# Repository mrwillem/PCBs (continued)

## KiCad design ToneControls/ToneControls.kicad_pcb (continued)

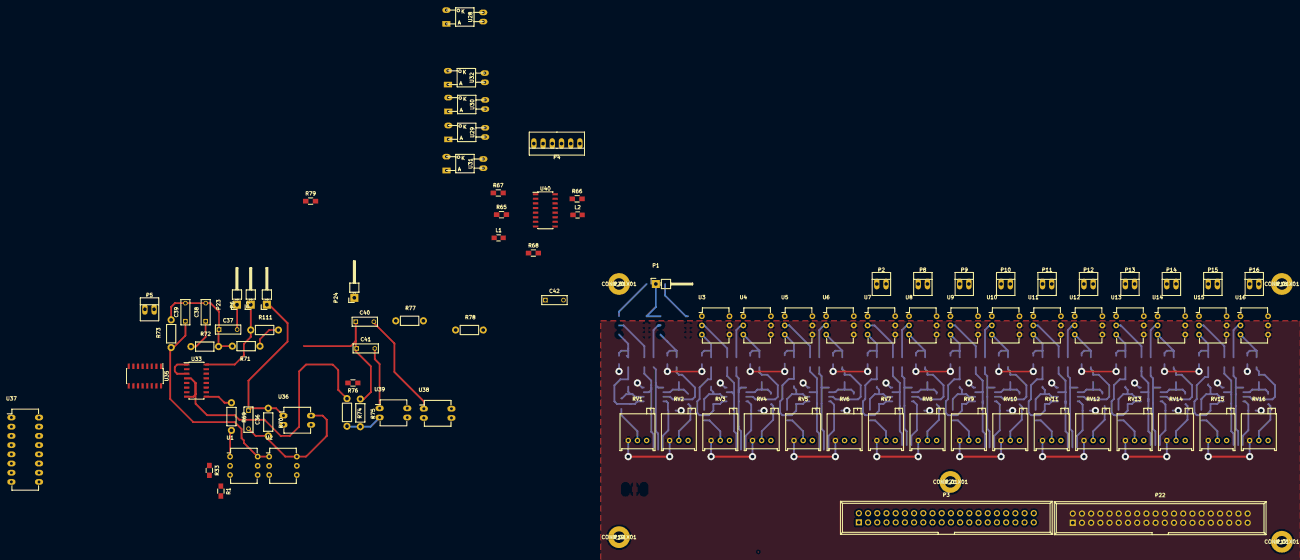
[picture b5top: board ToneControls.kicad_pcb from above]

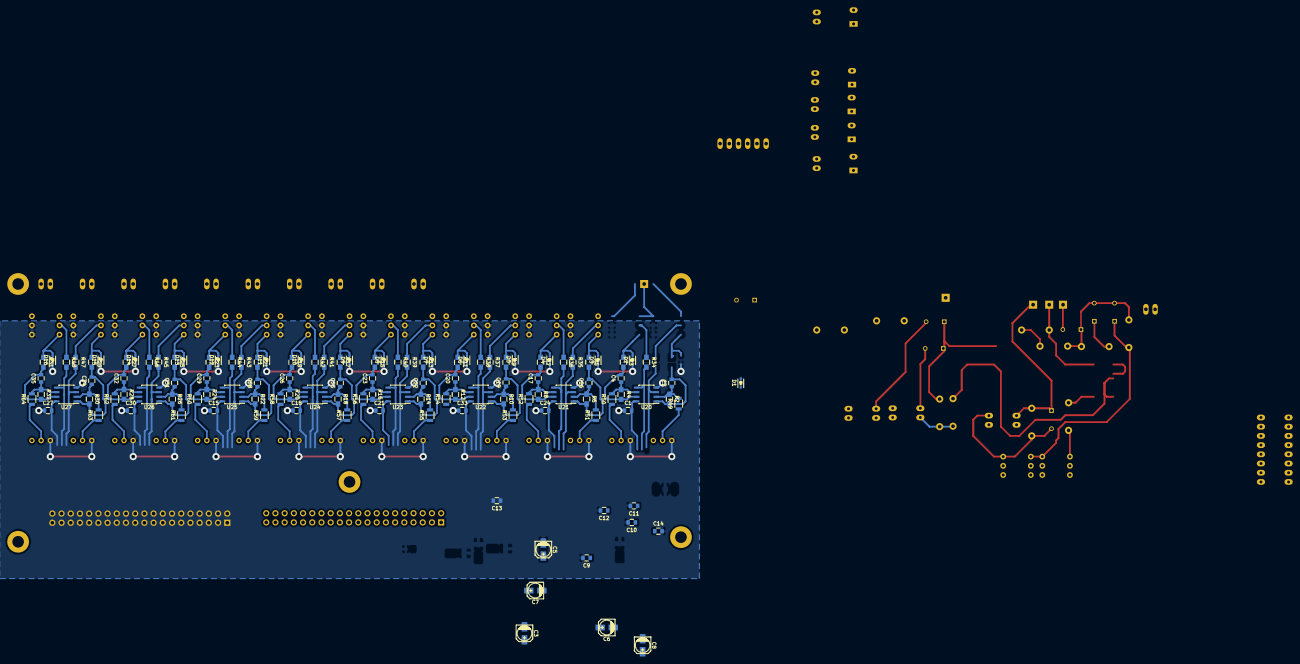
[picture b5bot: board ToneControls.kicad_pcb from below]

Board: 2 copper layers, 216 parts (121 on the bottom side), 160 nets.

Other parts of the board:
P9, P10: CONN_01X02; PINHEAD1-2

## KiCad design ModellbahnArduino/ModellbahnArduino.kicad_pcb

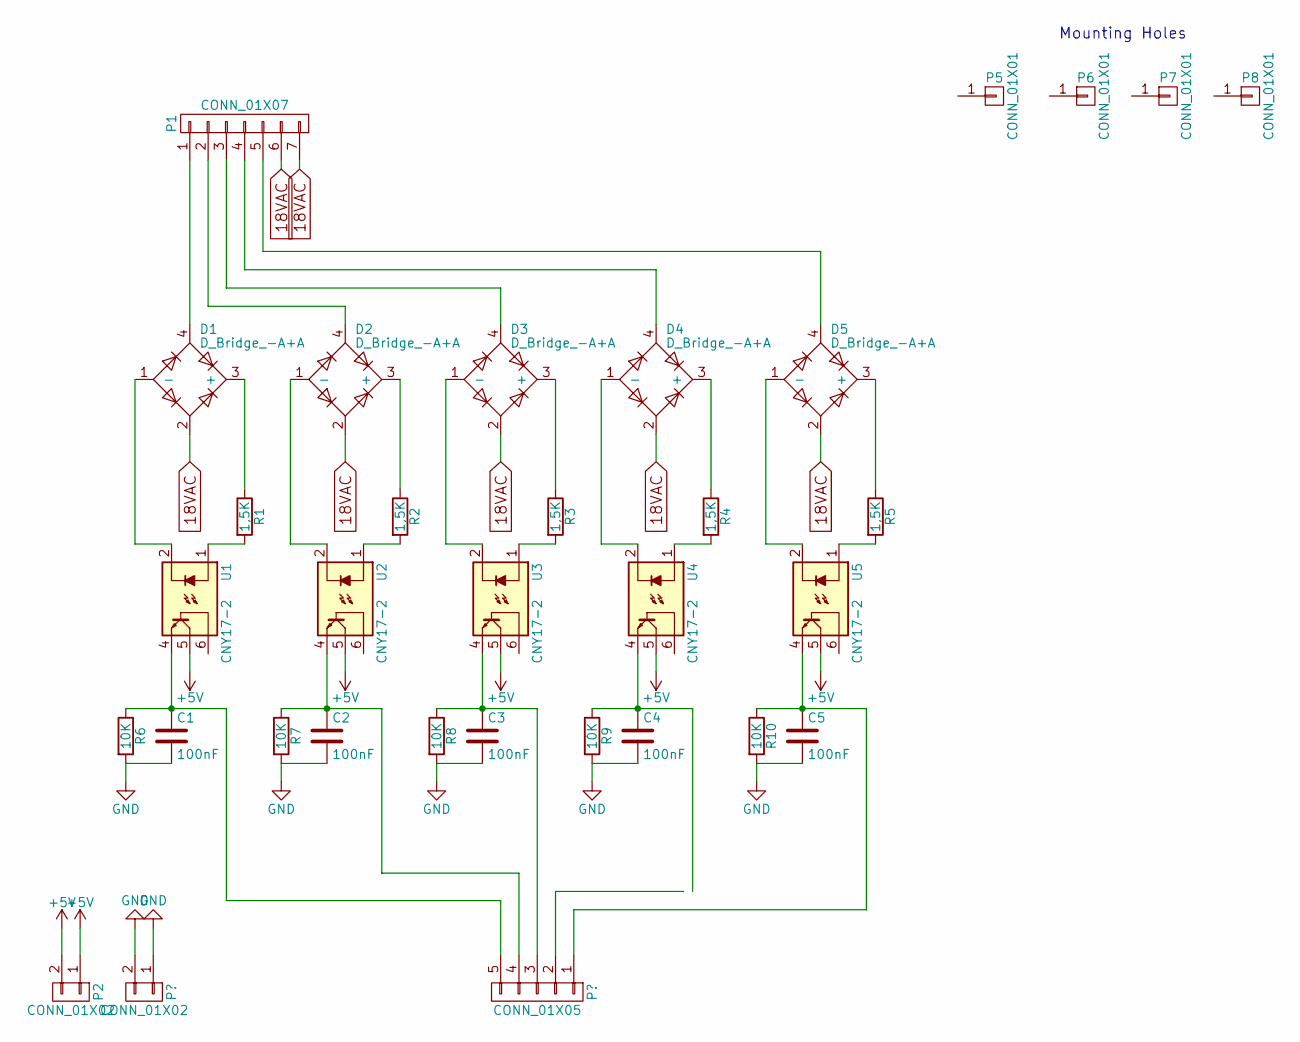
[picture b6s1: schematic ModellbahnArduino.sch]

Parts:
C1, C2, C3, C4, C5: 100nF; C_Disc_D5.0mm_W2.5mm_P2.50mm
D1, D2, D3, D4, D5: D_Bridge_-A+A; Diode_Bridge_9mm
P1: CONN_01X07; Pin_Header_Straight_1x07_Pitch2.54mm
P2: CONN_01X02; Pin_Header_Straight_1x02_Pitch2.54mm
P5, P6, P7, P8: CONN_01X01; MountingHole_3.2mm_M3_ISO7380
R1, R2, R3, R4, R5: 1,5K; R_Axial_DIN0207_L6.3mm_D2.5mm_P7.62mm_Horizontal
R6, R7, R8, R9, R10: 10K; R_Axial_DIN0207_L6.3mm_D2.5mm_P7.62mm_Horizontal
U1, U2, U3, U4, U5: CNY17-2; DIP-6_W7.62mm_LongPads

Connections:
18VAC: D1.2, D2.2, D3.2, D4.2, D5.2, P1.6, P1.7; also elsewhere on the board
+5V: P2.1, P2.2, U1.5, U2.5, U3.5, U4.5, U5.5
GND: C1.2, C2.2, C3.2, C4.2, C5.2, R6.2, R7.2, R8.2, R9.2, R10.2; also elsewhere on the board
unnamed: D1.1 (-), U1.2
unnamed: D1.3 (+), R1.1
unnamed: D1.4, P1.1
unnamed: D2.1 (-), U2.2
unnamed: D2.3 (+), R2.1
unnamed: D2.4, P1.2
unnamed: D3.1 (-), U3.2
unnamed: D3.3 (+), R3.1
unnamed: D3.4, P1.3
unnamed: D4.1 (-), U4.2
unnamed: D4.3 (+), R4.1
unnamed: D4.4, P1.4
unnamed: D5.1 (-), U5.2
unnamed: D5.3 (+), R5.1
unnamed: D5.4, P1.5
unnamed: R1.2, U1.1
unnamed: R2.2, U2.1
unnamed: R3.2, U3.1
unnamed: R4.2, U4.1
unnamed: R5.2, U5.1
OUT1: C1.1, R6.1, U1.4; also elsewhere on the board
OUT2: C2.1, R7.1, U2.4; also elsewhere on the board
OUT3: C3.1, R8.1, U3.4; also elsewhere on the board
OUT4: C4.1, R9.1, U4.4; also elsewhere on the board
OUT5: C5.1, R10.1, U5.4; also elsewhere on the board

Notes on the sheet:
Mounting Holes

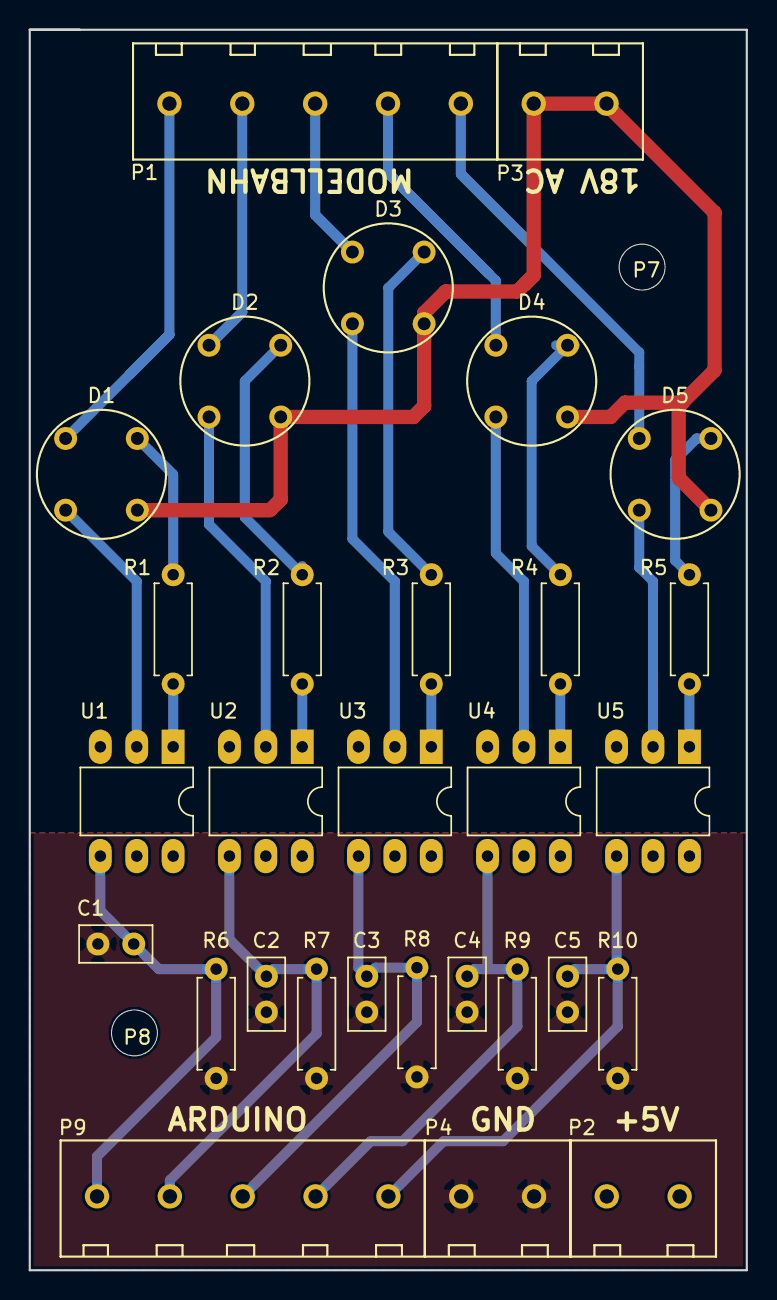
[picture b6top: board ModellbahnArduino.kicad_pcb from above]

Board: 2 copper layers, 50.0 x 86.5 mm, 32 parts (0 on the bottom side), 28 nets.

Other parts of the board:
P3, P4: CONN_01X02; Pin_Header_Straight_1x02_Pitch5.08mmDegson
P9: CONN_01X05; Pin_Header_Straight_1x05_Pitch5.08mmDegson

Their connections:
18VAC: P3.1, P3.2; also elsewhere on the board
GND: P4.1, P4.2; also elsewhere on the board
OUT1: P9.1; also elsewhere on the board
OUT2: P9.2; also elsewhere on the board
OUT3: P9.3; also elsewhere on the board
OUT4: P9.4; also elsewhere on the board
OUT5: P9.5; also elsewhere on the board

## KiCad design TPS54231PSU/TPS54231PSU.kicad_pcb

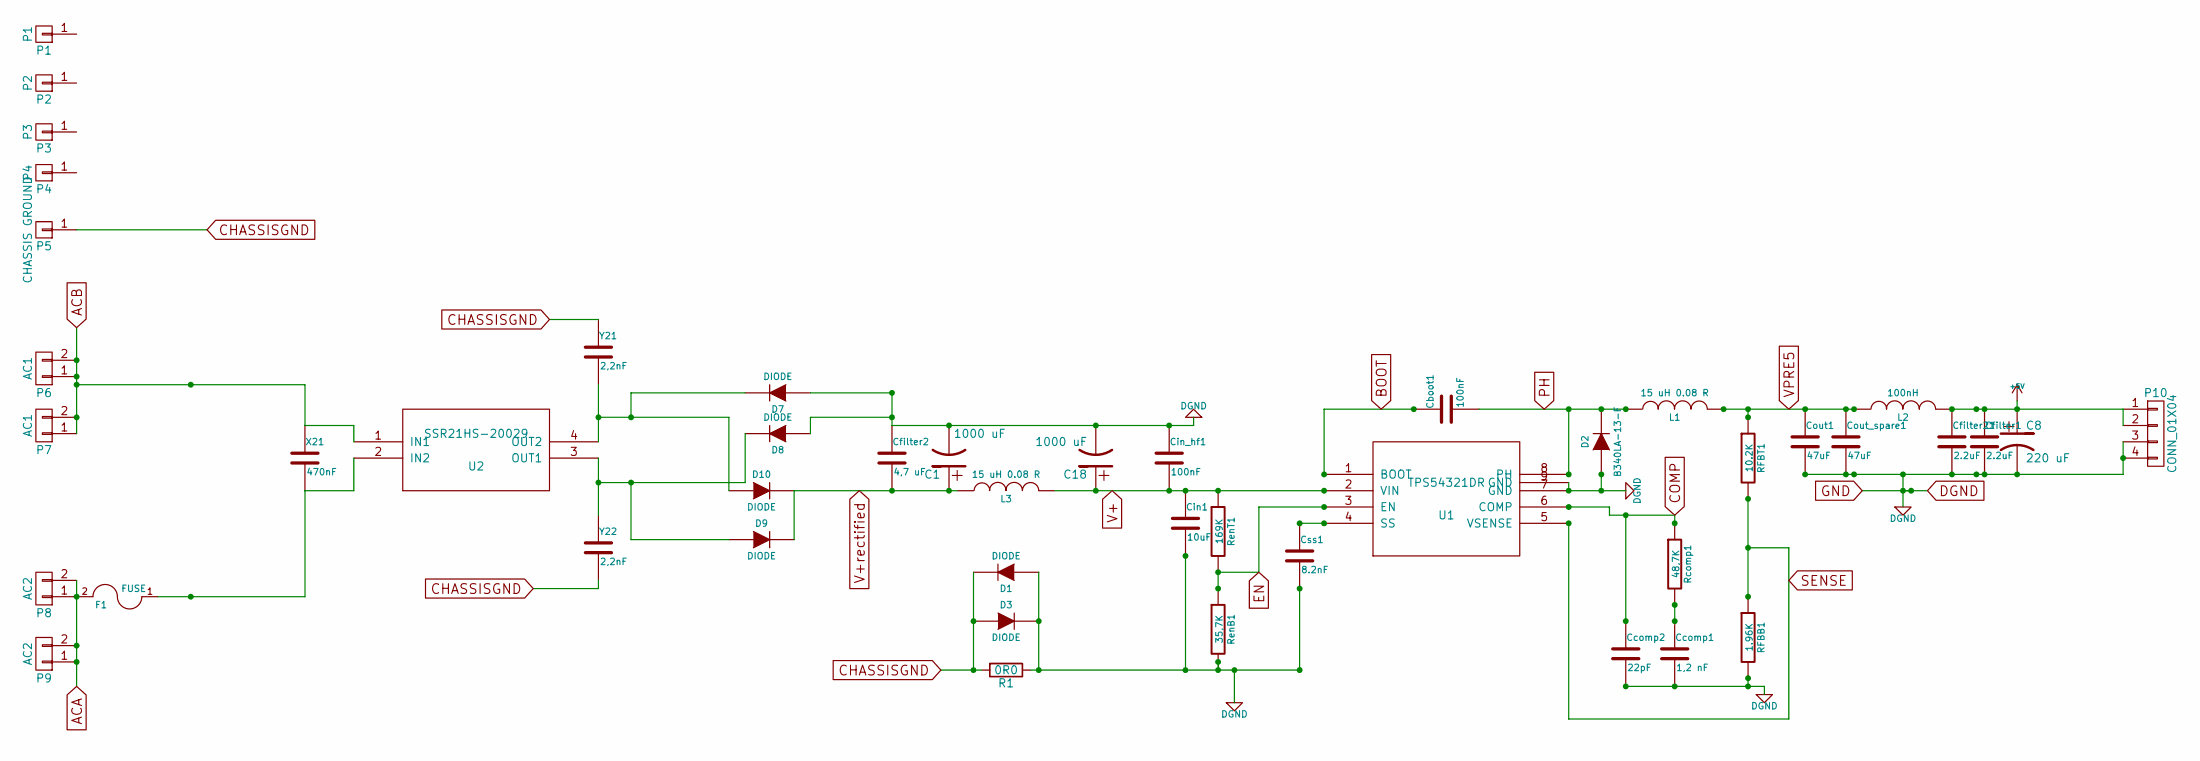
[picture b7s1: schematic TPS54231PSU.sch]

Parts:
C1, C18: 1000 uF; c_elec_12,5x15
C8: 220 uF; c_elec_8x10.5
Cboot1: 100nF; C_0805
Ccomp1: 1,2 nF; C_0805
Ccomp2: 22pF; C_0805
Cfilter1, Cfilter21: 2.2uF; C_0805
Cfilter2: 4,7 uF; C_1206
Cin1: 10uF; C_1206
Cin_hf1: 100nF; C_0805
Cout1: 47uF; C_1206
Cout_spare1: 47uF; C_1206
Css1: 8.2nF; C_0805
D1, D3, D7, D8, D9, D10: DIODE; SMA_Handsoldering
D2: B340LA-13-F; SMA_Handsoldering
F1: FUSE; FSUPCMS
L1, L3: 15 uH 0.08 R; inductor_bourns_16uH
L2: 100nH; Choke_SMD_Wuerth-WE-PD-Typ-M-Typ-S_Handsoldering_RevA_27Jul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
P1: P1; hole
P2: P2; hole
P3: P3; hole
P4: P4; hole
P5: CHASSIS GROUND; M4_Connect_Hole
P6, P7: AC1; Flat_Connector_635mm_
P8, P9: AC2; Flat_Connector_635mm_
P10: CONN_01X04; PINHEAD1-4
R1: 0R0; R_1206
RFBB1: 1.96K; R_0805
RFBT1: 10.2K; R_0805
Rcomp1: 48,7K; R_0805
RenB1: 35,7K; R_0805
RenT1: 169K; R_0805
U1: TPS54321DR; SOIC-8-1EP_3.9x4.9mm_Pitch1.27mm
U2: SSR21HS-20029; CommonModeChoke_KEMET_SSR21HS
X21: 470nF; C_Rect_L27_W9_H17_P23
Y21, Y22: 2,2nF; C_Rect_L18_W5_P15

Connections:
+5V: C8.1, Cfilter1.1, Cfilter21.1, L2.2, P10.1, P10.2
ACA: F1.2, P8.1, P8.2, P9.1, P9.2
ACB: P6.1, P6.2, P7.1, P7.2, U2.1 (IN1), X21.1
BOOT: Cboot1.1, U1.1 (BOOT)
CHASSISGND: D1.2 (K), D3.1 (A), P5.1, R1.2, Y21.1, Y22.2
COMP: Ccomp2.1, Rcomp1.1, U1.6 (COMP)
DGND: C1.2, C8.2, C18.2, Ccomp1.2, Ccomp2.2, Cfilter1.2, Cfilter2.1, Cfilter21.2, Cin1.2, Cin_hf1.1, Cout1.2, Cout_spare1.2, Css1.2, D1.1 (A), D2.1 (A), D3.2 (K), D7.1 (A), D8.1 (A), P10.3, P10.4, R1.1, RFBB1.2, RenB1.2, U1.7 (GND), U1.9 (GND)
EN: RenB1.1, RenT1.2, U1.3 (EN)
unnamed: Ccomp1.1, Rcomp1.2
unnamed: Css1.1, U1.4 (SS)
unnamed: D8.2 (K), D9.1 (A), U2.3 (OUT1), Y22.1
unnamed: D7.2 (K), D10.1 (A), U2.4 (OUT2), Y21.2
unnamed: F1.1, U2.2 (IN2), X21.2
PH: Cboot1.2, D2.2 (K), L1.1, U1.8 (PH)
SENSE: RFBB1.1, RFBT1.2, U1.5 (VSENSE)
V+: C18.1, Cin1.1, Cin_hf1.2, L3.2, RenT1.1, U1.2 (VIN)
V+rectified: C1.1, Cfilter2.2, D9.2 (K), D10.2 (K), L3.1
VPRE5: Cout1.1, Cout_spare1.1, L1.2, L2.1, RFBT1.1

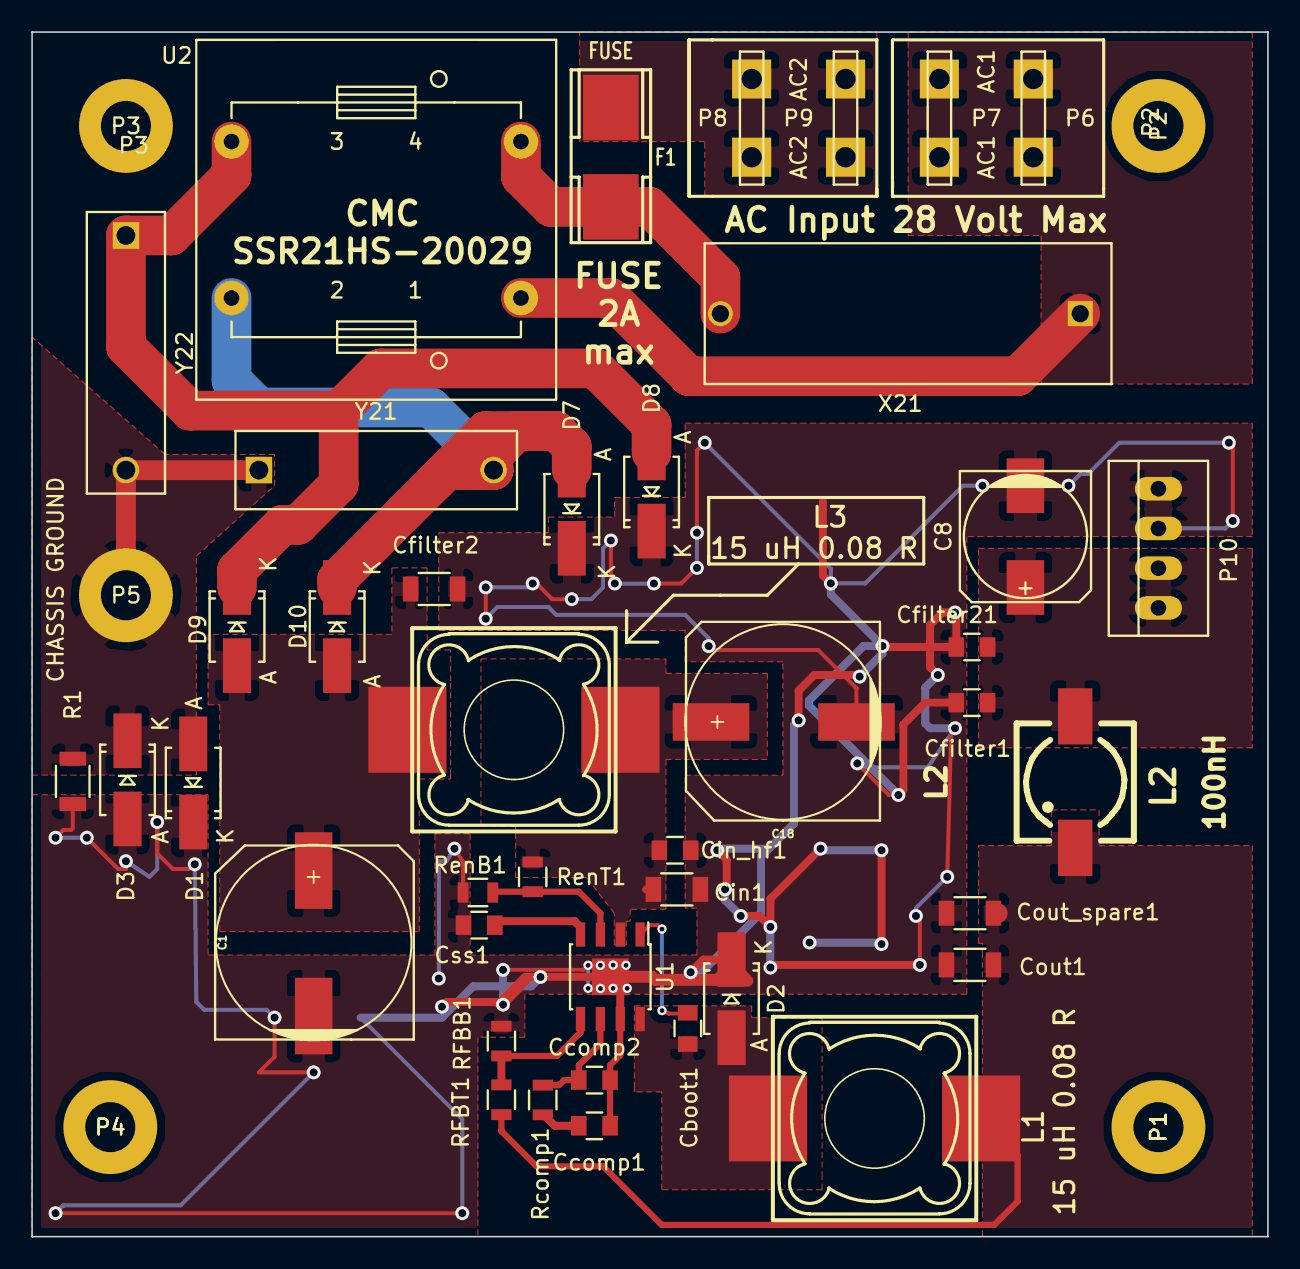
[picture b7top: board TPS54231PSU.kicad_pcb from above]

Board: 4 copper layers, 79.0 x 77.0 mm, 46 parts (0 on the bottom side), 18 nets.

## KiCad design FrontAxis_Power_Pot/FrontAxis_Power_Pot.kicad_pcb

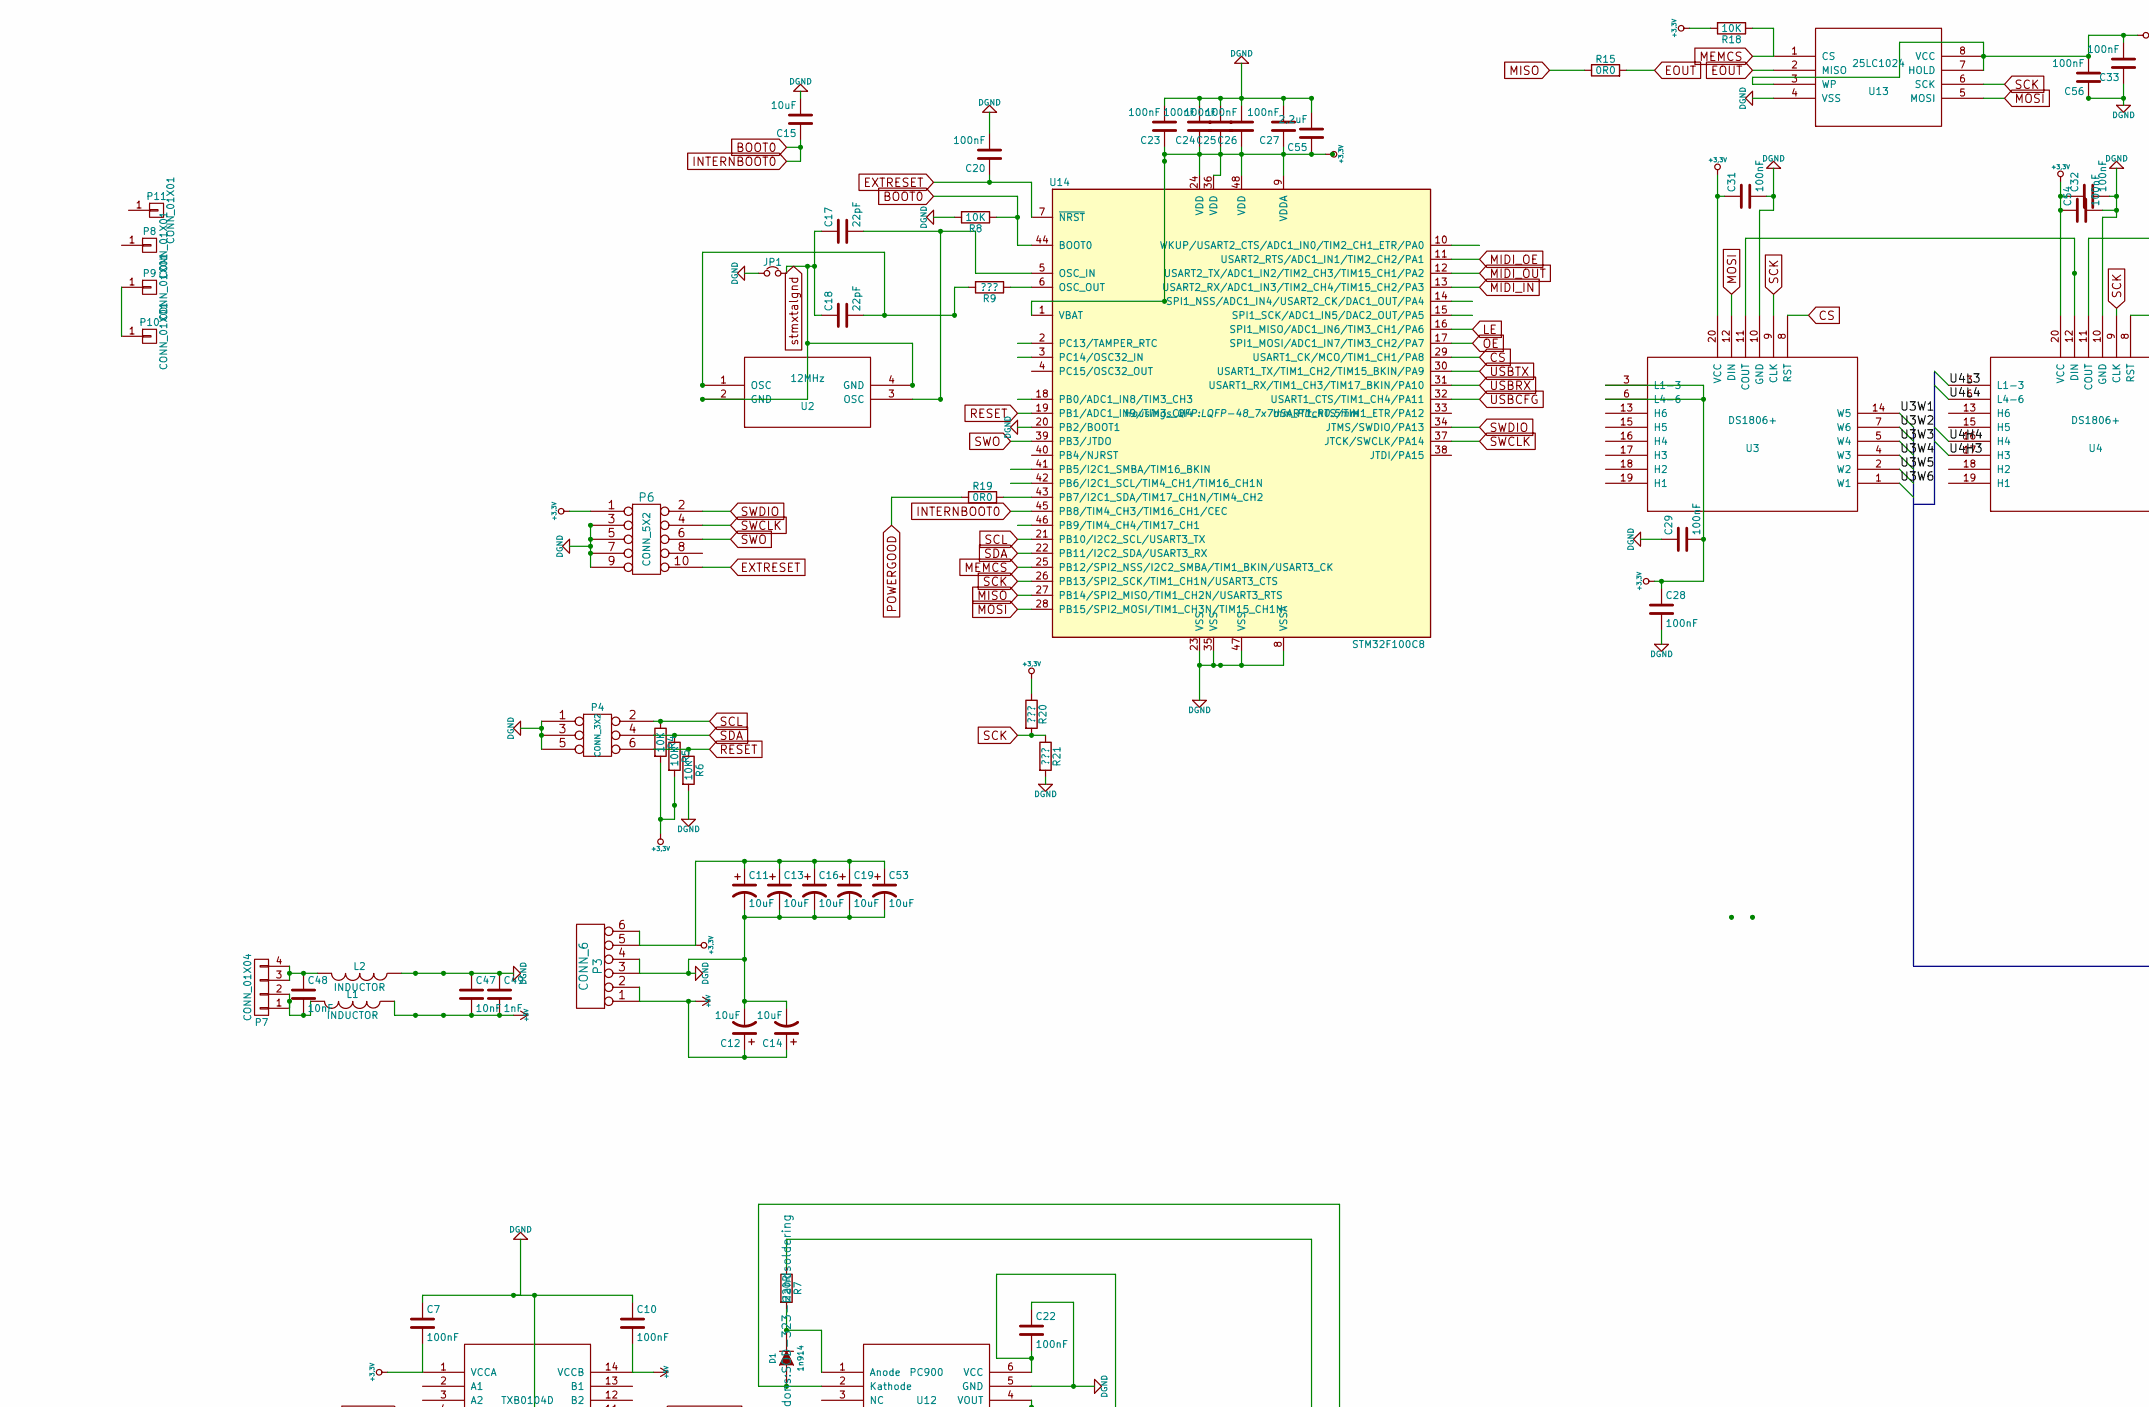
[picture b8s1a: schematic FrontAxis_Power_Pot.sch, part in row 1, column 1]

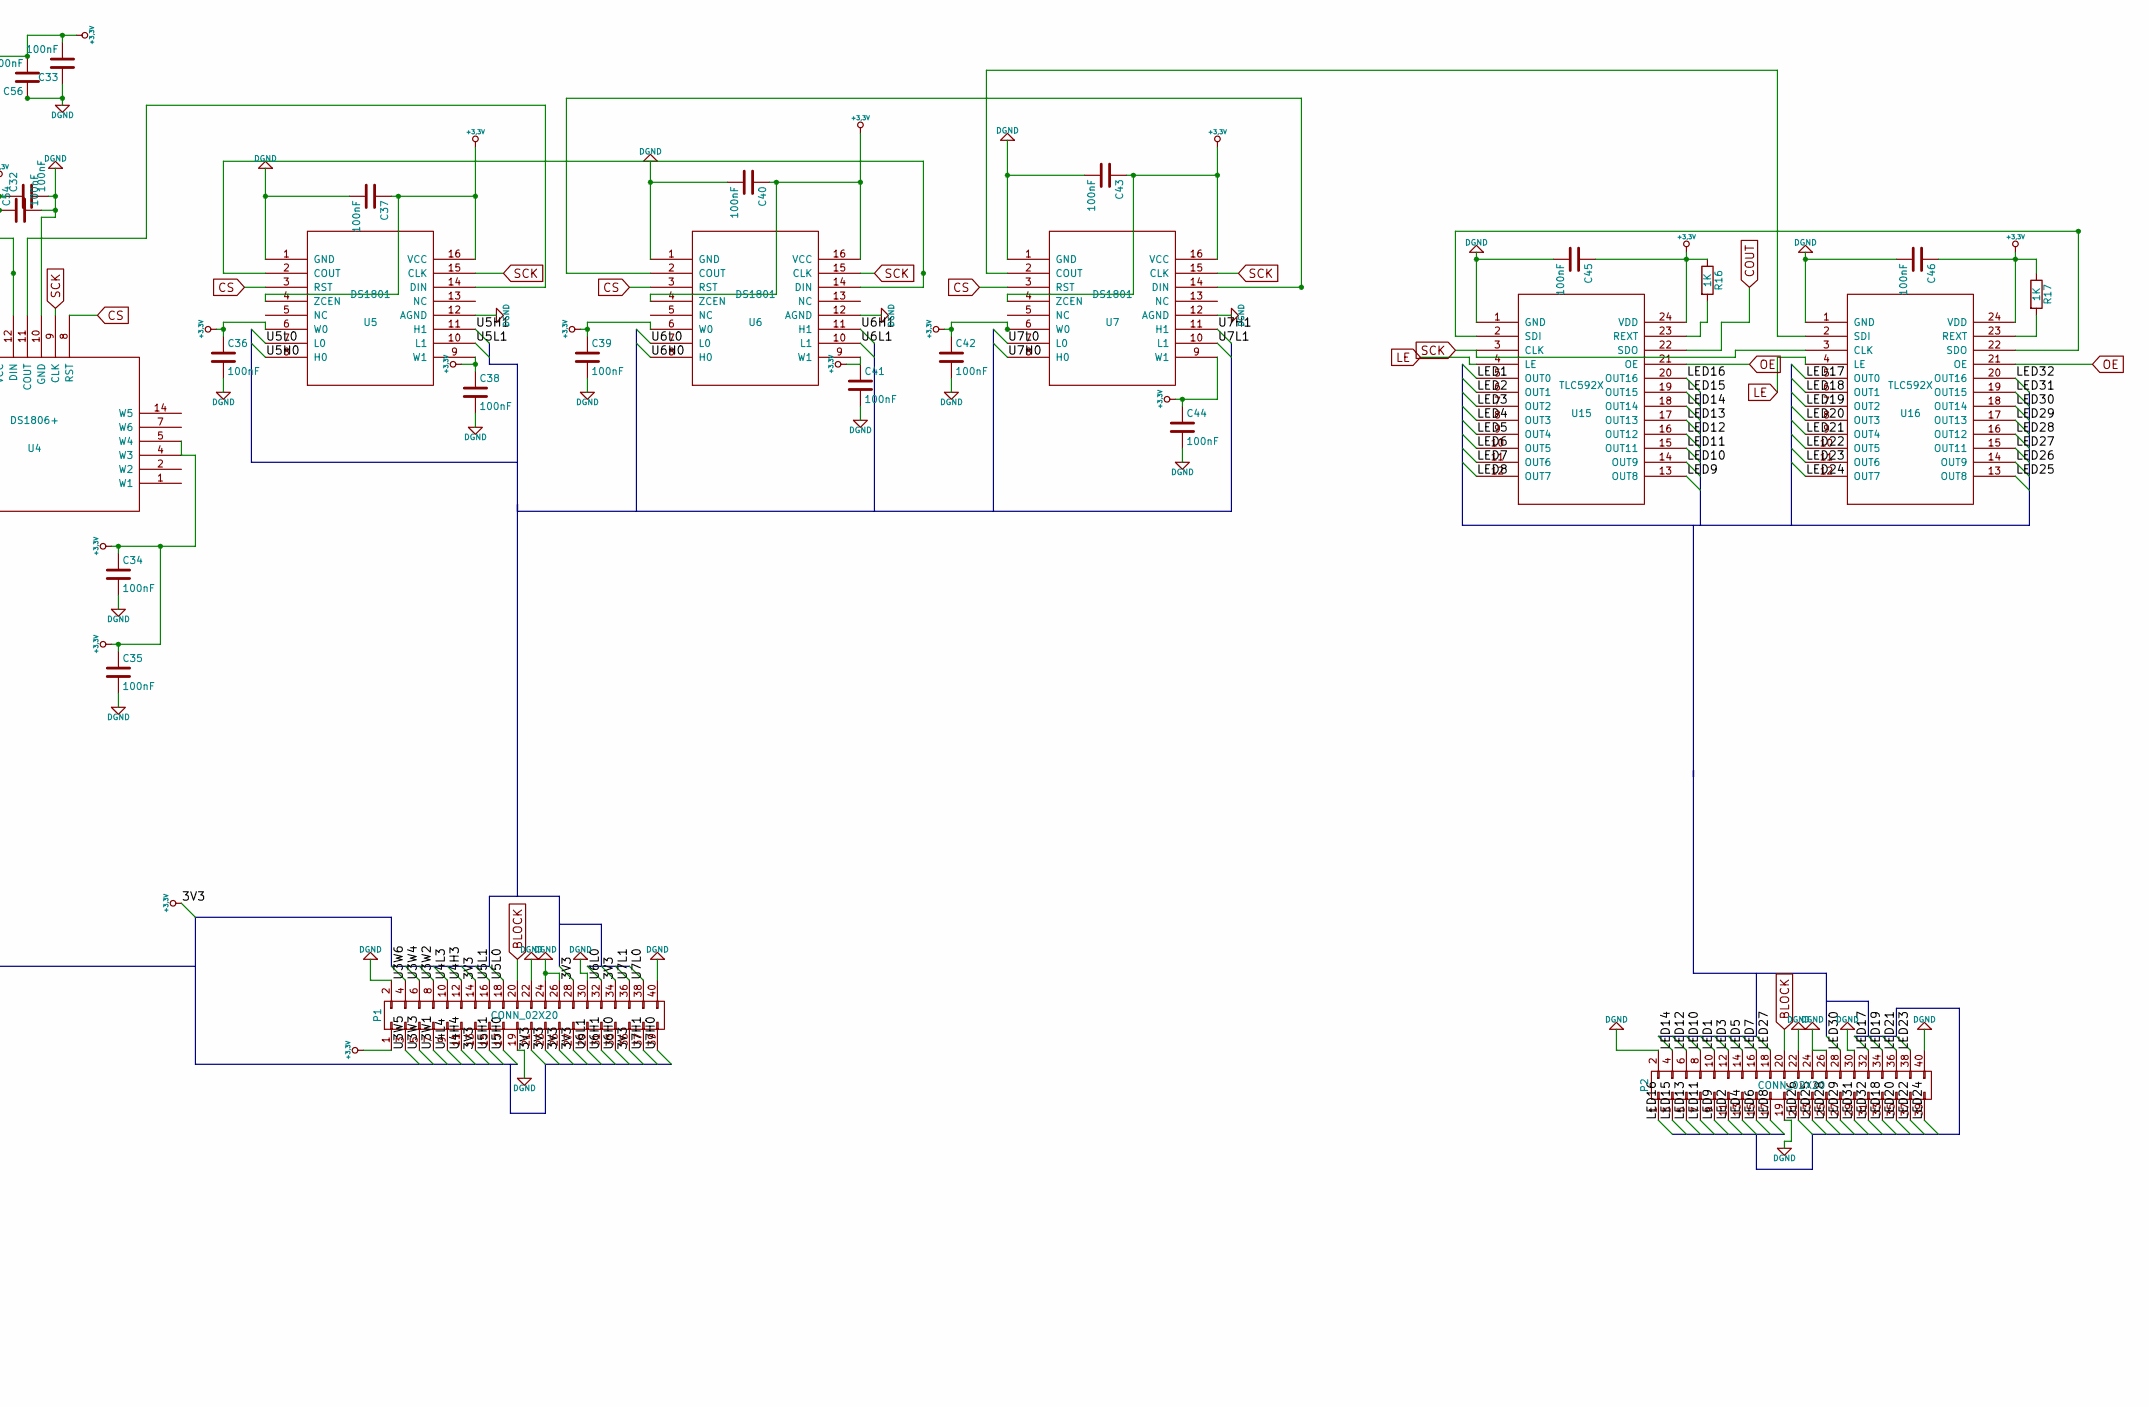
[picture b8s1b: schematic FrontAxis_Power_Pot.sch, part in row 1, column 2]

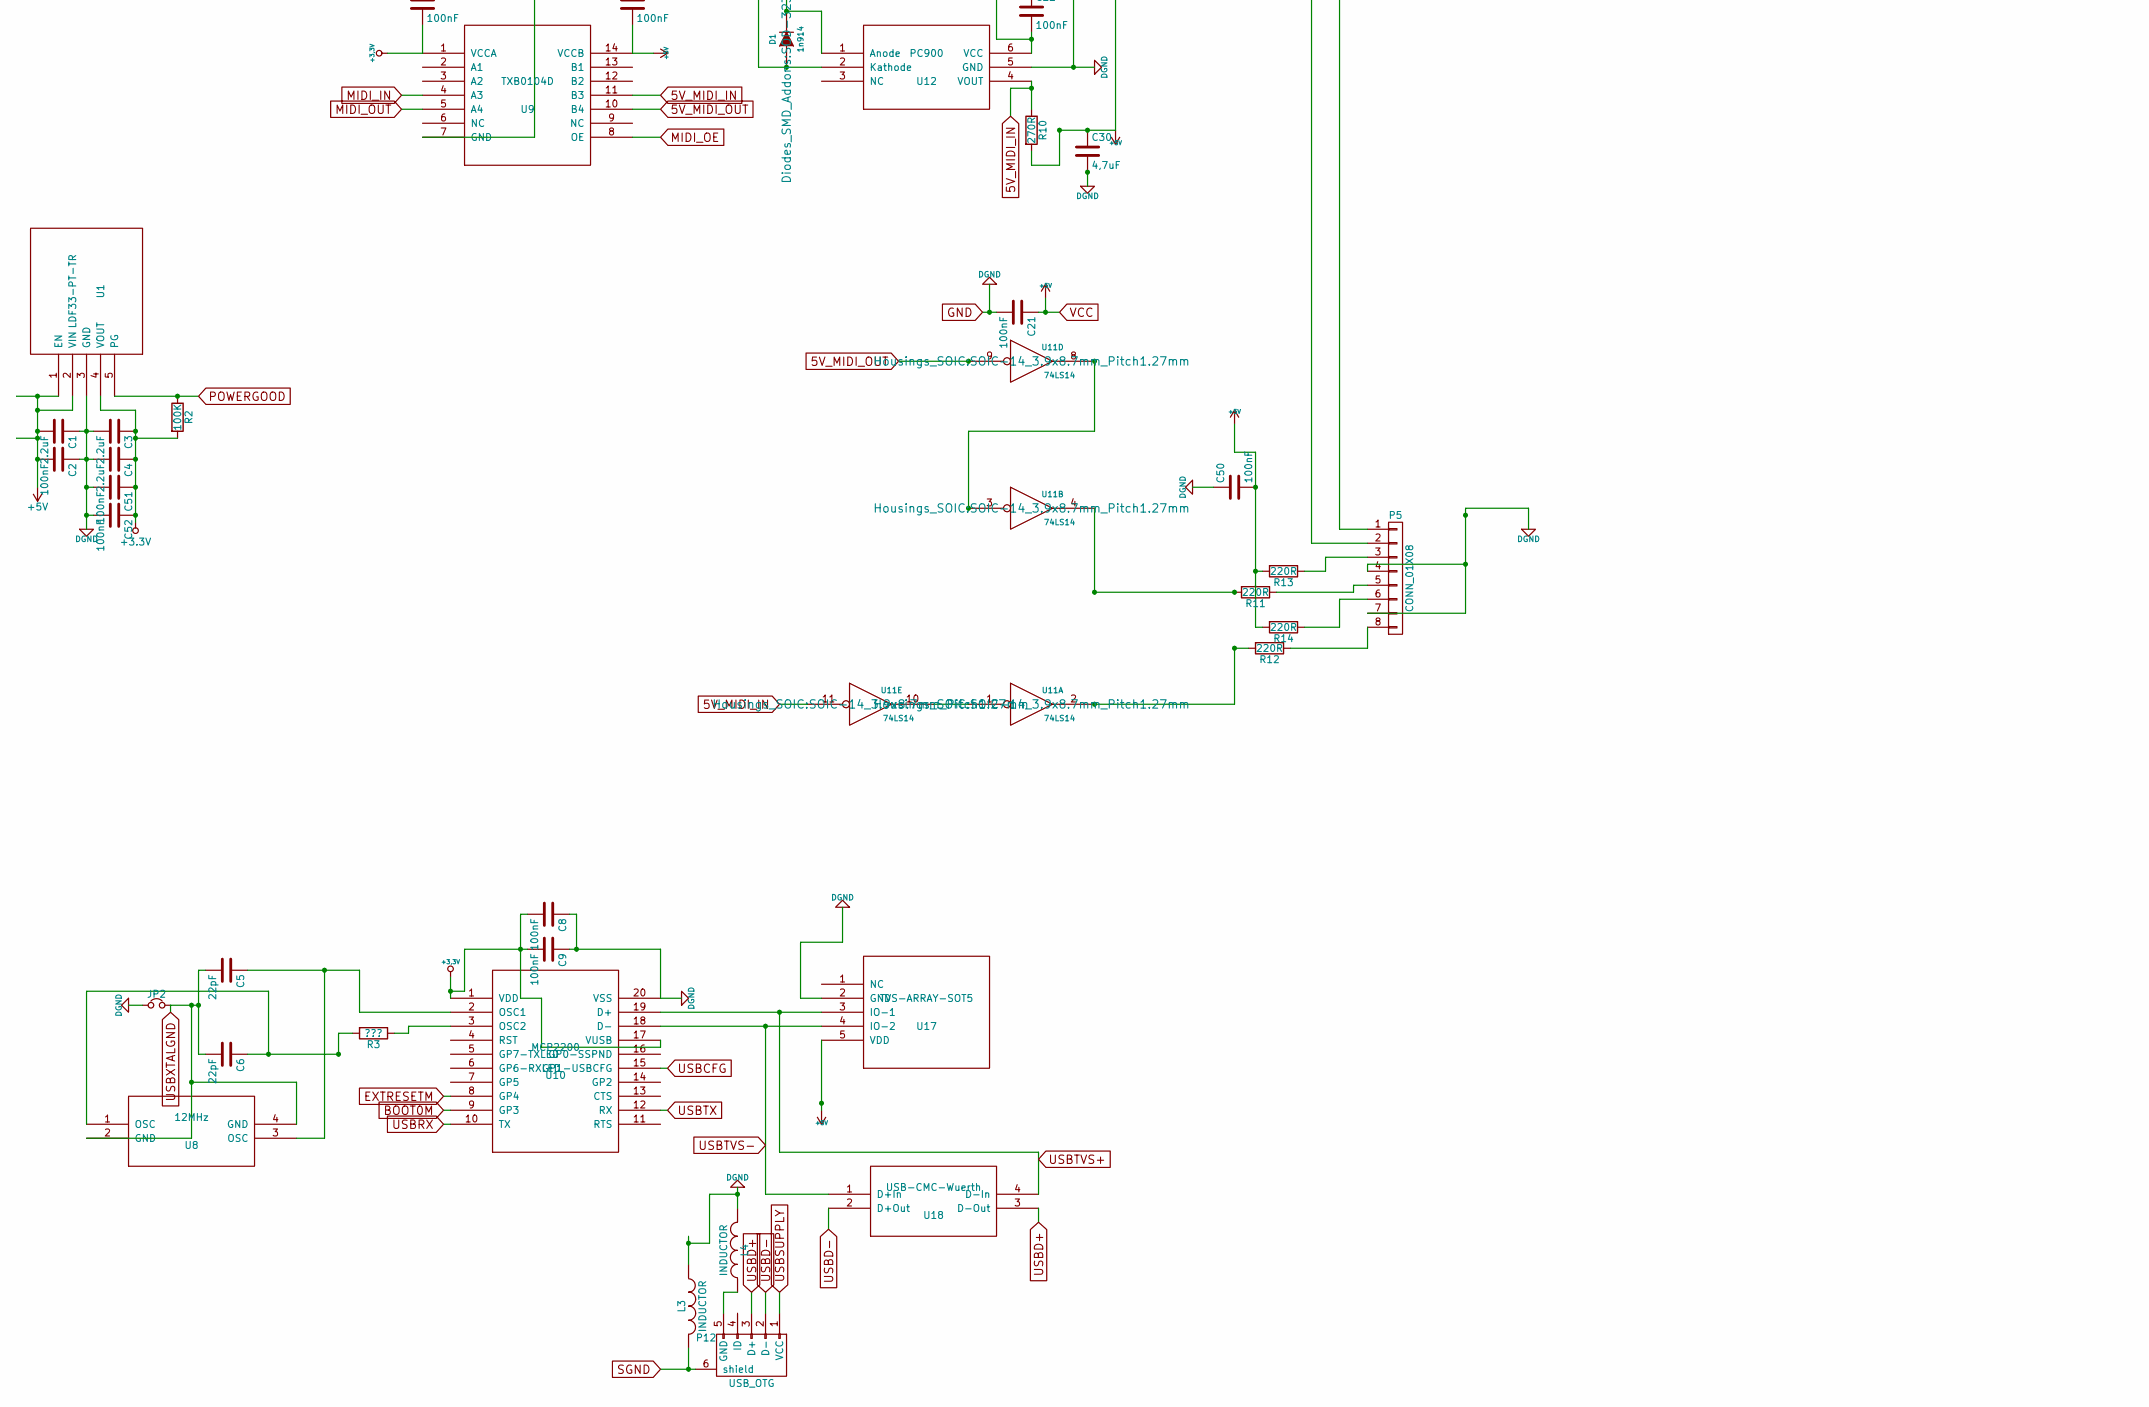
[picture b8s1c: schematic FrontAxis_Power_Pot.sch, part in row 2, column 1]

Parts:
C1, C3, C4: 2.2uF; C_0805
C2, C7, C8, C9, C10, C20, C21, C22, C23, C24, C25, C26, C27, C28, C29, C31, C32, C33, C34, C35, C36, C37, C38, C39, C40, C41, C42, C43, C44, C45, C46, C50, C51, C52, C54, C56: 100nF; C_0805
C5, C6, C17, C18: 22pF; C_0805
C11, C12, C13, C14, C16, C19, C53: 10uF; c_elec_4x5.8
C15: 10uF; C_1210
C30: 4,7uF; C_1210
C47, C48: 10nF; C_0805
C49: 1nF; C_0805
C55: 2,2uF; C_0805
D1: 1n914; SOD-323-Handsoldering
JP1, JP2: Jumper_NC_Small; NetTie-I_Connected_SMD
L1, L2: INDUCTOR; Choke_SMD_1206_Standard
L3, L4: INDUCTOR; C_0805
P1, P2: CONN_02X20; IDC_Header_Straight_40pins
P3: CONN_6; PINHEAD1-6
P4: CONN_3X2; con-amp-micromatch-MICROMATCH-6-correct
P5: CONN_01X08; PINHEAD1-8
P6: CONN_5X2; Pin_Header_Straight_2x05_Pitch1.27mm
P7: CONN_01X04; PINHEAD1-4
P8, P9, P10, P11: CONN_01X01; hole
P12: USB_OTG; USB_Mini-B
R2: 100K; R_0805_HandSoldering
R3: ???; R_0805_HandSoldering
R4, R5, R6, R8, R18: 10K; R_0805_HandSoldering
R7, R11, R12, R13, R14: 220R; R_0805_HandSoldering
R9, R20, R21: ???; R_0603_HandSoldering
R10: 270R; R_0805_HandSoldering
R15: 0R0; R_0805_HandSoldering
R16, R17: 1K; R_0805_HandSoldering
R19: 0R0; R_1206
U1: LDF33-PT-TR; TO-252-4Lead
U2, U8: 12MHz; Xtal_Ceramic_5x3.2
U3, U4: DS1806+; SOIC-20_7.5x12.8mm_Pitch1.27mm
U5, U6, U7: DS1801; SOIC-16_7.5x10.3mm_Pitch1.27mm
U9: TXB0104D; SOIC-14_3.9x8.7mm_Pitch1.27mm
U10: MCP2200; SOIC-20_7.5x12.8mm_Pitch1.27mm
U11: 74LS14; SOIC-14_3.9x8.7mm_Pitch1.27mm
U12: PC900; SO6_DIL_GULLWING
U13: 25LC1024; SOIC-8_3.9x4.9mm_Pitch1.27mm
U14: STM32F100C8; LQFP-48_7x7mm_Pitch0.5mm
U15, U16: TLC592X; SOIC-24_7.5x15.4mm_Pitch1.27mm
U17: TVS-ARRAY-SOT5; SOT-23-5
U18: USB-CMC-Wuerth; CMC-SMD-Wuerth

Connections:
5V_MIDI_IN: R10.1, U9.11 (B3), U11.11, U12.4 (VOUT)
5V_MIDI_OUT: U9.10 (B4), U11.9
/LED1: P2.10, U15.5 (OUT0)
/LED2: P2.11, U15.6 (OUT1)
/LED3: P2.12, U15.7 (OUT2)
/LED4: P2.13, U15.8 (OUT3)
/LED5: P2.14, U15.9 (OUT4)
/LED6: P2.15, U15.10 (OUT5)
/LED7: P2.16, U15.11 (OUT6)
/LED8: P2.17, U15.12 (OUT7)
/LED9: P2.9, U15.13 (OUT8)
/LED10: P2.8, U15.14 (OUT9)
/LED11: P2.7, U15.15 (OUT11)
/LED12: P2.6, U15.16 (OUT12)
/LED13: P2.5, U15.17 (OUT13)
/LED14: P2.4, U15.18 (OUT14)
/LED15: P2.3, U15.19 (OUT15)
/LED16: P2.1, U15.20 (OUT16)
/LED17: P2.32, U16.5 (OUT0)
/LED18: P2.33, U16.6 (OUT1)
/LED19: P2.34, U16.7 (OUT2)
/LED20: P2.35, U16.8 (OUT3)
/LED21: P2.36, U16.9 (OUT4)
/LED22: P2.37, U16.10 (OUT5)
/LED23: P2.38, U16.11 (OUT6)
/LED24: P2.39, U16.12 (OUT7)
/LED25: P2.23, U16.13 (OUT8)
/LED26: P2.21, U16.14 (OUT9)
/LED27: P2.18, U16.15 (OUT11)
/LED28: P2.25, U16.16 (OUT12)
/LED29: P2.27, U16.17 (OUT13)
/LED30: P2.28, U16.18 (OUT14)
/LED31: P2.29, U16.19 (OUT15)
/LED32: P2.31, U16.20 (OUT16)
/U3W1: P1.7, U3.14 (W5)
/U3W2: P1.8, U3.7 (W6)
/U3W3: P1.5, U3.5 (W4)
/U3W4: P1.6, U3.4 (W3)
/U3W5: P1.3, U3.2 (W2)
/U3W6: P1.4, U3.1 (W1)
/U4H3: P1.12, U4.17 (H3)
/U4H4: P1.11, U4.16 (H4)
/U4L3: P1.10, U4.3 (L1-3)
/U4L4: P1.9, U4.6 (L4-6)
/U5H0: P1.17, U5.8 (H0)
/U5H1: P1.15, U5.11 (H1)
/U5L0: P1.18, U5.7 (L0)
/U5L1: P1.16, U5.10 (L1)
/U6H0: P1.33, U6.8 (H0)
/U6H1: P1.31, U6.11 (H1)
/U6L0: P1.32, U6.7 (L0)
/U6L1: P1.29, U6.10 (L1)
/U7H0: P1.39, U7.8 (H0)
/U7H1: P1.37, U7.11 (H1)
/U7L0: P1.38, U7.7 (L0)
/U7L1: P1.36, U7.10 (L1)
BLOCK: P1.20, P2.20
BOOT0: C15.1, R8.1, U14.44 (BOOT0), U14.45 (PB8/TIM4_CH3/TIM16_CH1/CEC)
BOOT0M: U10.9 (GP3)
COUT: U15.22 (SDO)
CS: U3.8 (RST), U4.8 (RST), U5.3 (RST), U6.3 (RST), U7.3 (RST), U14.29 (USART1_CK/MCO/TIM1_CH1/PA8)
EOUT: R15.2, U13.2 (MISO)
EXTRESET: C20.1, P6.10, U14.7 (~NRST)
EXTRESETM: U10.8 (GP4)
LE: U14.16 (SPI1_MISO/ADC1_IN6/TIM3_CH1/PA6), U15.4 (LE), U16.4 (LE)
MEMCS: R18.1, U13.1 (CS), U14.25 (PB12/SPI2_NSS/I2C2_SMBA/TIM1_BKIN/USART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)
MIDI_IN: U9.4 (A3), U14.13 (USART2_RX/ADC1_IN3/TIM2_CH4/TIM15_CH2/P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)
MIDI_OE: U9.8 (OE), U14.11 (USART2_RTS/ADC1_IN1/TIM2_CH2/PA1)
MIDI_OUT: U9.5 (A4), U14.12 (USART2_TX/ADC1_IN2/TIM2_CH3/TIM15_CH1/P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)
MISO: R15.1, U14.27 (PB14/SPI2_MISO/TIM1_CH2N/USART3_RTS)
MOSI: U3.12 (DIN), U13.5 (MOSI), U14.28 (PB15/SPI2_MOSI/TIM1_CH3N/TIM15_CH1N)
unnamed: C5.1, U8.3 (OSC), U10.2 (OSC1)
unnamed: C6.1, R3.2, U8.1 (OSC)
unnamed: C17.2, U2.3 (OSC), U14.5 (OSC_IN)
unnamed: C18.2, R9.2, U2.1 (OSC)
unnamed: C48.1, L2.2, P7.3, P7.4
unnamed: C48.2, L1.2, P7.1, P7.2
unnamed: D1.1 (A), P5.1, U12.2 (Kathode)
unnamed: D1.2 (K), R7.2, U12.1 (Anode)
unnamed: L4.1, P12.5 (GND)
unnamed: P5.2, R7.1
unnamed: P5.3, R13.1
unnamed: P5.5, R11.1
unnamed: P5.6, R14.1
unnamed: P5.8, R12.1
unnamed: R3.1, U10.3 (OSC2)
unnamed: R9.1, U14.6 (OSC_OUT)
unnamed: R11.2, U11.4
unnamed: R12.2, U11.2
unnamed: R16.2, U15.23 (REXT)
unnamed: R17.2, U16.23 (REXT)
unnamed: R19.2, U14.43 (PB7/I2C1_SDA/TIM17_CH1N/TIM4_CH2)
unnamed: U3.11 (COUT), U4.12 (DIN)
unnamed: U4.11 (COUT), U5.14 (DIN)
unnamed: U6.2 (COUT), U7.14 (DIN)
unnamed: U11.1, U11.10
unnamed: U11.3, U11.8
unnamed: U15.2 (SDI), U16.22 (SDO)
unnamed: U7.2 (COUT), U16.2 (SDI)
OE: U14.17 (SPI1_MOSI/ADC1_IN7/TIM3_CH2/PA7), U15.21 (OE), U16.21 (OE)
POWERGOOD: R2.1, R19.1, U1.5 (PG)
RESET: P4.6, R6.1, U14.19 (PB1/ADC1_IN9/TIM3_CH4)
SCK: R20.2, R21.1, U3.9 (CLK), U4.9 (CLK), U5.15 (CLK), U6.15 (CLK), U7.15 (CLK), U13.6 (SCK), U14.26 (PB13/SPI2_SCK/TIM1_CH1N/USART3_CTS), U15.3 (CLK), U16.3 (CLK)
SCL: P4.2, R4.1, U14.21 (PB10/I2C2_SCL/USART3_TX)
SDA: P4.4, R5.1, U14.22 (PB11/I2C2_SDA/USART3_RX)
SGND: L3.2, P12.6 (shield)
SWCLK: P6.4, U14.37 (JTCK/SWCLK/PA14)
SWDIO: P6.2, U14.34 (JTMS/SWDIO/PA13)
SWO: P6.6, U14.39 (PB3/JTDO)
USBCFG: U10.15 (GP1-USBCFG), U14.32 (USART1_CTS/TIM1_CH4/PA11)
USBD+: P12.3 (D+), U18.3 (D-Out)
USBD-: P12.2 (D-), U18.2 (D+Out)
USBRX: U10.10 (TX), U14.31 (USART1_RX/TIM1_CH3/TIM17_BKIN/PA10)
USBSUPPLY: P12.1 (VCC)
USBTVS+: U10.19 (D+), U17.3 (IO-1), U18.4 (D-In)
USBTVS-: U10.18 (D-), U17.4 (IO-2), U18.1 (D+In)
USBTX: U10.12 (RX), U14.30 (USART1_TX/TIM1_CH2/TIM15_BKIN/PA9)
USBXTALGND: C5.2, C6.2, JP2.2, U8.2 (GND), U8.4 (GND)
VCC: C1.2, C2.2, C10.2, C12.1, C14.1, C21.1, C22.2, C30.1, C47.2, C49.2, C50.2, L1.1, P3.1, P3.2, R10.2, R13.2, R14.2, U1.1 (EN), U1.2 (VIN), U9.14 (VCCB), U11.14 (VCC), U12.6 (VCC), U17.5 (VDD)
stmxtalgnd: C17.1, C18.1, JP1.2, U2.2 (GND), U2.4 (GND)

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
